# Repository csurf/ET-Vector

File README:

Eagle Tree Vector Flight Controller

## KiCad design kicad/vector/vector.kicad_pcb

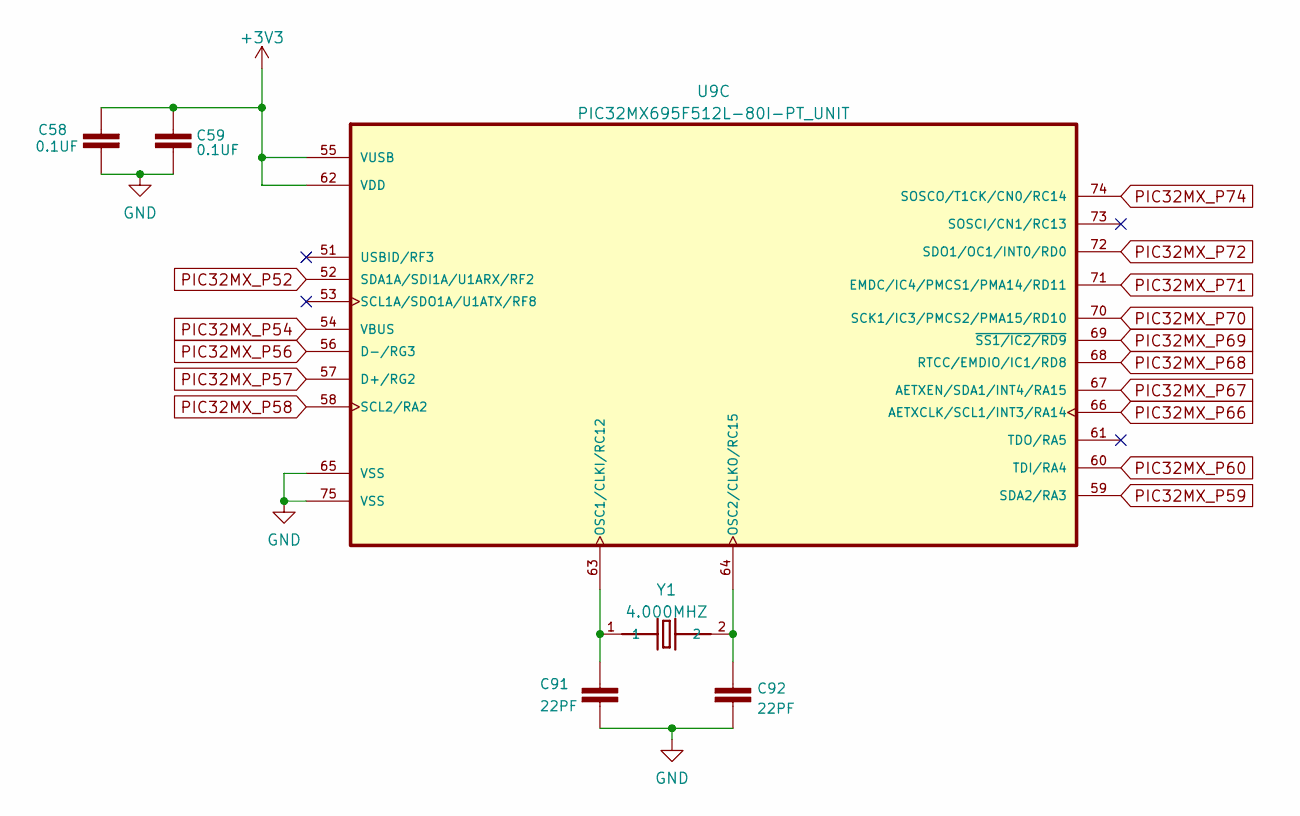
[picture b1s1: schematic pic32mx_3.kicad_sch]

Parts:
C58, C59: 0.1UF; C_0402_1005Metric
C91, C92: 22PF; C_0402_1005Metric
U9: PIC32MX695F512L-80I-PT_UNIT; TQFP-100_12x12mm_P0.4mm
Y1: 4.000MHZ; Crystal_SMD_HC49-SD

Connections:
+3V3: C58.2, C59.1, U9.55 (VUSB), U9.62 (VDD); also elsewhere on the board
GND: C58.1, C59.2, C91.2, C92.2, U9.65 (VSS), U9.75 (VSS); also elsewhere on the board
I2C_SCL2: U9.58 (SCL2/RA2); also elsewhere on the board
I2C_SDA2: U9.59 (SDA2/RA3); also elsewhere on the board
unnamed: C91.1, U9.63 (OSC1/CLKI/RC12), Y1.1
unnamed: C92.1, U9.64 (OSC2/CLKO/RC15), Y1.2
PIC32MX_P26: U9.68 (RTCC/EMDIO/IC1/RD8); also elsewhere on the board
PIC32MX_P40: U9.69 (~SS1/IC2/RD9); also elsewhere on the board
PIC32MX_P52: U9.52 (SDA1A/SDI1A/U1ARX/RF2), U9.71 (EMDC/IC4/PMCS1/PMA14/RD11); also elsewhere on the board
PIC32MX_P54: U9.54 (VBUS); also elsewhere on the board
PIC32MX_P56: U9.56 (D-/RG3); also elsewhere on the board
PIC32MX_P57: U9.57 (D+/RG2); also elsewhere on the board
PIC32MX_P60: U9.60 (TDI/RA4); also elsewhere on the board
PIC32MX_P66: U9.66 (AETXCLK/SCL1/INT3/RA14); also elsewhere on the board
PIC32MX_P67: U9.67 (AETXEN/SDA1/INT4/RA15); also elsewhere on the board
PIC32MX_P70: U9.70 (SCK1/IC3/PMCS2/PMA15/RD10); also elsewhere on the board
PIC32MX_P72: U9.72 (SDO1/OC1/INT0/RD0); also elsewhere on the board
PIC32MX_P74: U9.74 (SOSCO/T1CK/CN0/RC14); also elsewhere on the board

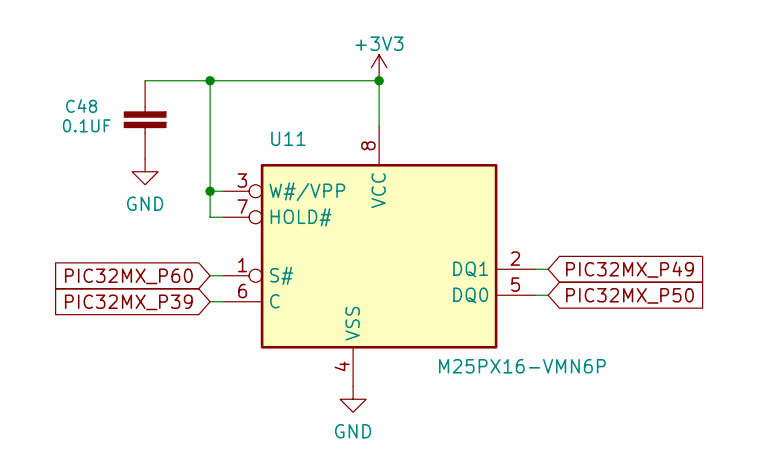
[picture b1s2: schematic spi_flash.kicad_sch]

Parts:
C48: 0.1UF; C_0402_1005Metric
U11: M25PX16-VMN6P; SOIC-8_3.9x4.9mm_P1.27mm

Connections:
+3V3: C48.2, U11.3 (W#/VPP), U11.7 (HOLD#), U11.8 (VCC); also elsewhere on the board
GND: C48.1, U11.4 (VSS); also elsewhere on the board
PIC32MX_P39: U11.6 (C); also elsewhere on the board
PIC32MX_P49: U11.2 (DQ1); also elsewhere on the board
PIC32MX_P50: U11.5 (DQ0); also elsewhere on the board
PIC32MX_P60: U11.1 (S#); also elsewhere on the board

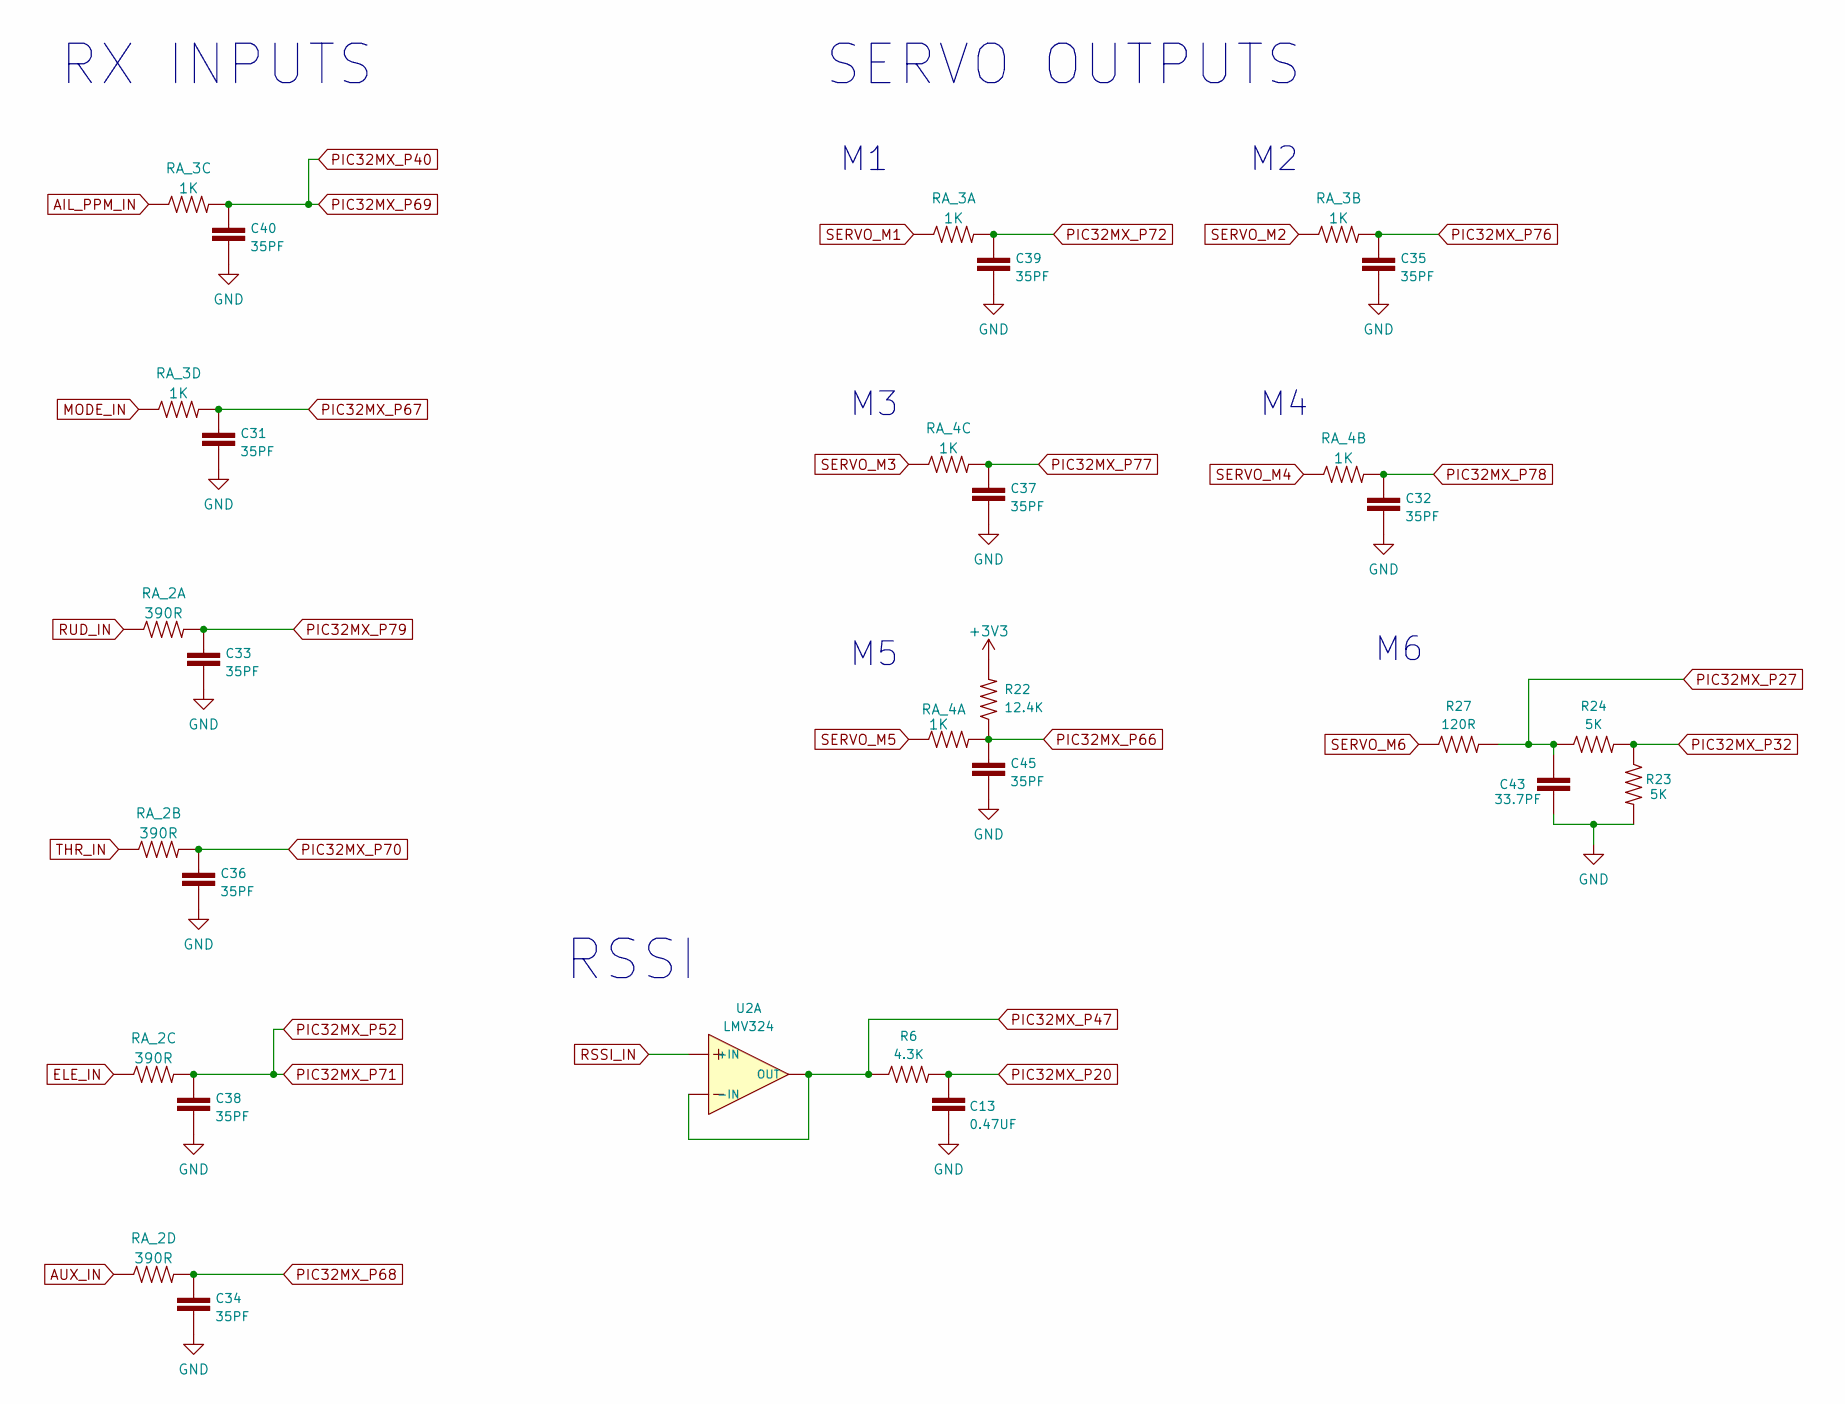
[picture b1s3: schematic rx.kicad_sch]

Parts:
C13: 0.47UF; C_0402_1005Metric
C31, C32, C33, C34, C35, C36, C37, C38, C39, C40, C45: 35PF; C_0402_1005Metric
C43: 33.7PF; C_0402_1005Metric
R6: 4.3K; R_0402_1005Metric
R22: 12.4K; R_0402_1005Metric
R23, R24: 5K; R_0402_1005Metric
R27: 120R; R_0402_1005Metric
RA_2: 390R; R_Array_Convex_4x0402
RA_3, RA_4: 1K; R_Array_Convex_4x0402
U2: LMV324; TSSOP-14_4.4x5mm_P0.65mm

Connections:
+3V3: R22.2; also elsewhere on the board
AIL_PPM_IN: RA_3.3 (1); also elsewhere on the board
AUX_IN: RA_2.4 (1); also elsewhere on the board
ELE_IN: RA_2.3 (1); also elsewhere on the board
GND: C13.2, C31.2, C32.2, C33.2, C34.2, C35.2, C36.2, C37.2, C38.2, C39.2, C40.2, C43.2, C45.2, R23.2; also elsewhere on the board
MODE_IN: RA_3.4 (1); also elsewhere on the board
PIC32MX_P20: C13.1, R6.2; also elsewhere on the board
PIC32MX_P26: C34.1, RA_2.5 (2); also elsewhere on the board
PIC32MX_P27: C43.1, R24.1, R27.2; also elsewhere on the board
PIC32MX_P32: R23.1, R24.2; also elsewhere on the board
PIC32MX_P40: C40.1, RA_3.6 (2); also elsewhere on the board
PIC32MX_P47: R6.1, U2.1 (OUT), U2.2 (-IN); also elsewhere on the board
PIC32MX_P52: C38.1, RA_2.6 (2); also elsewhere on the board
PIC32MX_P66: C45.1, R22.1, RA_4.8 (2); also elsewhere on the board
PIC32MX_P67: C31.1, RA_3.5 (2); also elsewhere on the board
PIC32MX_P70: C36.1, RA_2.7 (2); also elsewhere on the board
PIC32MX_P72: C39.1, RA_3.8 (2); also elsewhere on the board
PIC32MX_P76: C35.1, RA_3.7 (2); also elsewhere on the board
PIC32MX_P77: C37.1, RA_4.6 (2); also elsewhere on the board
PIC32MX_P78: C32.1, RA_4.7 (2); also elsewhere on the board
PIC32MX_P79: C33.1, RA_2.8 (2); also elsewhere on the board
RSSI_IN: U2.3 (+IN); also elsewhere on the board
RUD_IN: RA_2.1; also elsewhere on the board
SERVO_M1: RA_3.1; also elsewhere on the board
SERVO_M2: RA_3.2 (1); also elsewhere on the board
SERVO_M3: RA_4.3 (1); also elsewhere on the board
SERVO_M4: RA_4.2 (1); also elsewhere on the board
SERVO_M5: RA_4.1; also elsewhere on the board
SERVO_M6: R27.1; also elsewhere on the board
THR_IN: RA_2.2 (1); also elsewhere on the board

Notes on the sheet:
SERVO OUTPUTS
RSSI
RX INPUTS

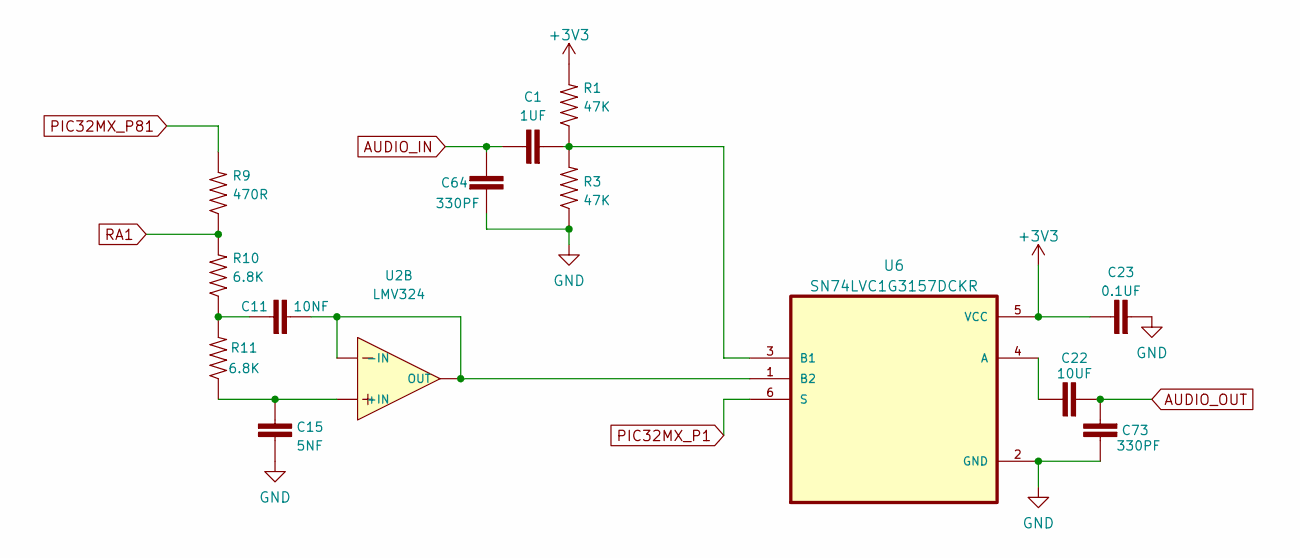
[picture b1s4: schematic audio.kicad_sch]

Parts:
C1: 1UF; C_0603_1608Metric
C11: 10NF; C_0402_1005Metric
C15: 5NF; C_0402_1005Metric
C22: 10UF; C_0603_1608Metric
C23: 0.1UF; C_0402_1005Metric
C64, C73: 330PF; C_0402_1005Metric
R1, R3: 47K; R_0402_1005Metric
R9: 470R; R_0402_1005Metric
R10, R11: 6.8K; R_0402_1005Metric
U2: LMV324; TSSOP-14_4.4x5mm_P0.65mm
U6: SN74LVC1G3157DCKR; Texas_R-PDSO-G6

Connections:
+3V3: C23.1, R1.2, U6.5 (VCC); also elsewhere on the board
AUDIO_IN: C1.1, C64.1; also elsewhere on the board
AUDIO_OUT: C22.2, C73.2; also elsewhere on the board
GND: C15.2, C23.2, C64.2, C73.1, R3.1, U6.2 (GND); also elsewhere on the board
unnamed: C1.2, R1.1, R3.2, U6.3 (B1)
unnamed: C11.1, R10.1, R11.2
unnamed: C11.2, U2.8 (OUT), U2.9 (-IN), U6.1 (B2)
unnamed: C15.1, R11.1, U2.10 (+IN)
unnamed: C22.1, U6.4 (A)
PIC32MX_P1: U6.6 (S); also elsewhere on the board
PIC32MX_P81: R9.2; also elsewhere on the board
RA1: R9.1, R10.2; also elsewhere on the board

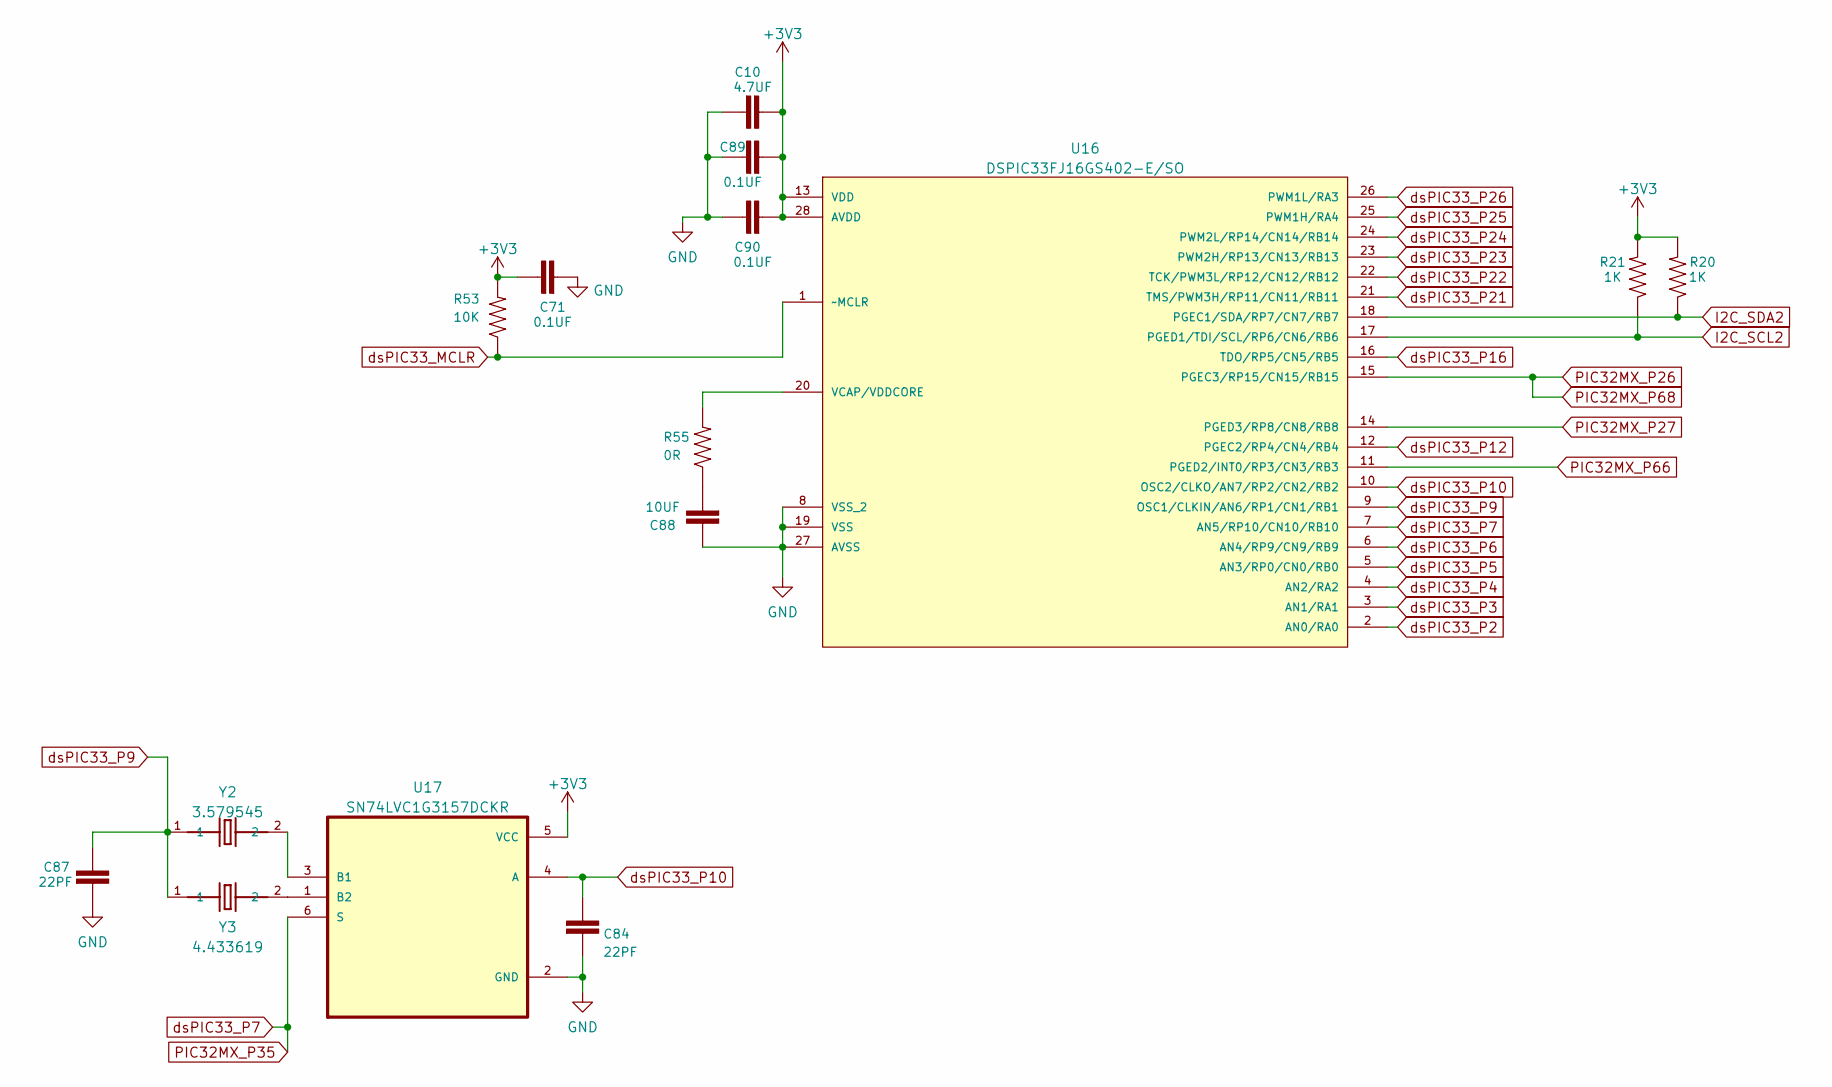
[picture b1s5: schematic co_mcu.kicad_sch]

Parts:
C10: 4.7UF; C_0603_1608Metric
C71, C89, C90: 0.1UF; C_0402_1005Metric
C84, C87: 22PF; C_0402_1005Metric
C88: 10UF; C_0805_2012Metric
R20, R21: 1K; R_0402_1005Metric
R53: 10K; R_0402_1005Metric
R55: 0R; R_0402_1005Metric
U16: DSPIC33FJ16GS402-E/SO; SOIC-28W_7.5x17.9mm_P1.27mm; MPN DSPIC33FJ16GS402-E/SO
U17: SN74LVC1G3157DCKR; Texas_R-PDSO-G6
Y2: 3.579545; Crystal_SMD_HC49-SD
Y3: 4.433619; Crystal_SMD_HC49-SD

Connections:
+3V3: C10.1, C71.1, C89.2, C90.2, R20.2, R21.2, R53.2, U16.13 (VDD), U16.28 (AVDD), U17.5 (VCC); also elsewhere on the board
GND: C10.2, C71.2, C84.2, C87.2, C88.1, C89.1, C90.1, U16.8 (VSS_2), U16.19 (VSS), U16.27 (AVSS), U17.2 (GND); also elsewhere on the board
I2C_SCL2: R21.1, U16.17 (PGED1/TDI/SCL/RP6/CN6/RB6); also elsewhere on the board
I2C_SDA2: R20.1, U16.18 (PGEC1/SDA/RP7/CN7/RB7); also elsewhere on the board
unnamed: C88.2, R55.1
unnamed: R55.2, U16.20 (VCAP/VDDCORE)
unnamed: U17.1 (B2), Y3.2
unnamed: U17.3 (B1), Y2.2
PIC32MX_P26: U16.15 (PGEC3/RP15/CN15/RB15); also elsewhere on the board
PIC32MX_P27: U16.14 (PGED3/RP8/CN8/RB8); also elsewhere on the board
PIC32MX_P35: U16.7 (AN5/RP10/CN10/RB10), U17.6 (S); also elsewhere on the board
PIC32MX_P66: U16.11 (PGED2/INT0/RP3/CN3/RB3); also elsewhere on the board
dsPIC33_MCLR: R53.1, U16.1 (~MCLR)
dsPIC33_P2: U16.2 (AN0/RA0); also elsewhere on the board
dsPIC33_P3: U16.3 (AN1/RA1); also elsewhere on the board
dsPIC33_P4: U16.4 (AN2/RA2); also elsewhere on the board
dsPIC33_P5: U16.5 (AN3/RP0/CN0/RB0); also elsewhere on the board
dsPIC33_P6: U16.6 (AN4/RP9/CN9/RB9); also elsewhere on the board
dsPIC33_P9: C87.1, U16.9 (OSC1/CLKIN/AN6/RP1/CN1/RB1), Y2.1, Y3.1
dsPIC33_P10: C84.1, U16.10 (OSC2/CLKO/AN7/RP2/CN2/RB2), U17.4 (A)
dsPIC33_P12: U16.12 (PGEC2/RP4/CN4/RB4); also elsewhere on the board
dsPIC33_P16: U16.16 (TDO/RP5/CN5/RB5); also elsewhere on the board
dsPIC33_P21: U16.21 (TMS/PWM3H/RP11/CN11/RB11); also elsewhere on the board
dsPIC33_P22: U16.22 (TCK/PWM3L/RP12/CN12/RB12); also elsewhere on the board
dsPIC33_P23: U16.23 (PWM2H/RP13/CN13/RB13); also elsewhere on the board
dsPIC33_P24: U16.24 (PWM2L/RP14/CN14/RB14); also elsewhere on the board
dsPIC33_P25: U16.25 (PWM1H/RA4); also elsewhere on the board
dsPIC33_P26: U16.26 (PWM1L/RA3); also elsewhere on the board

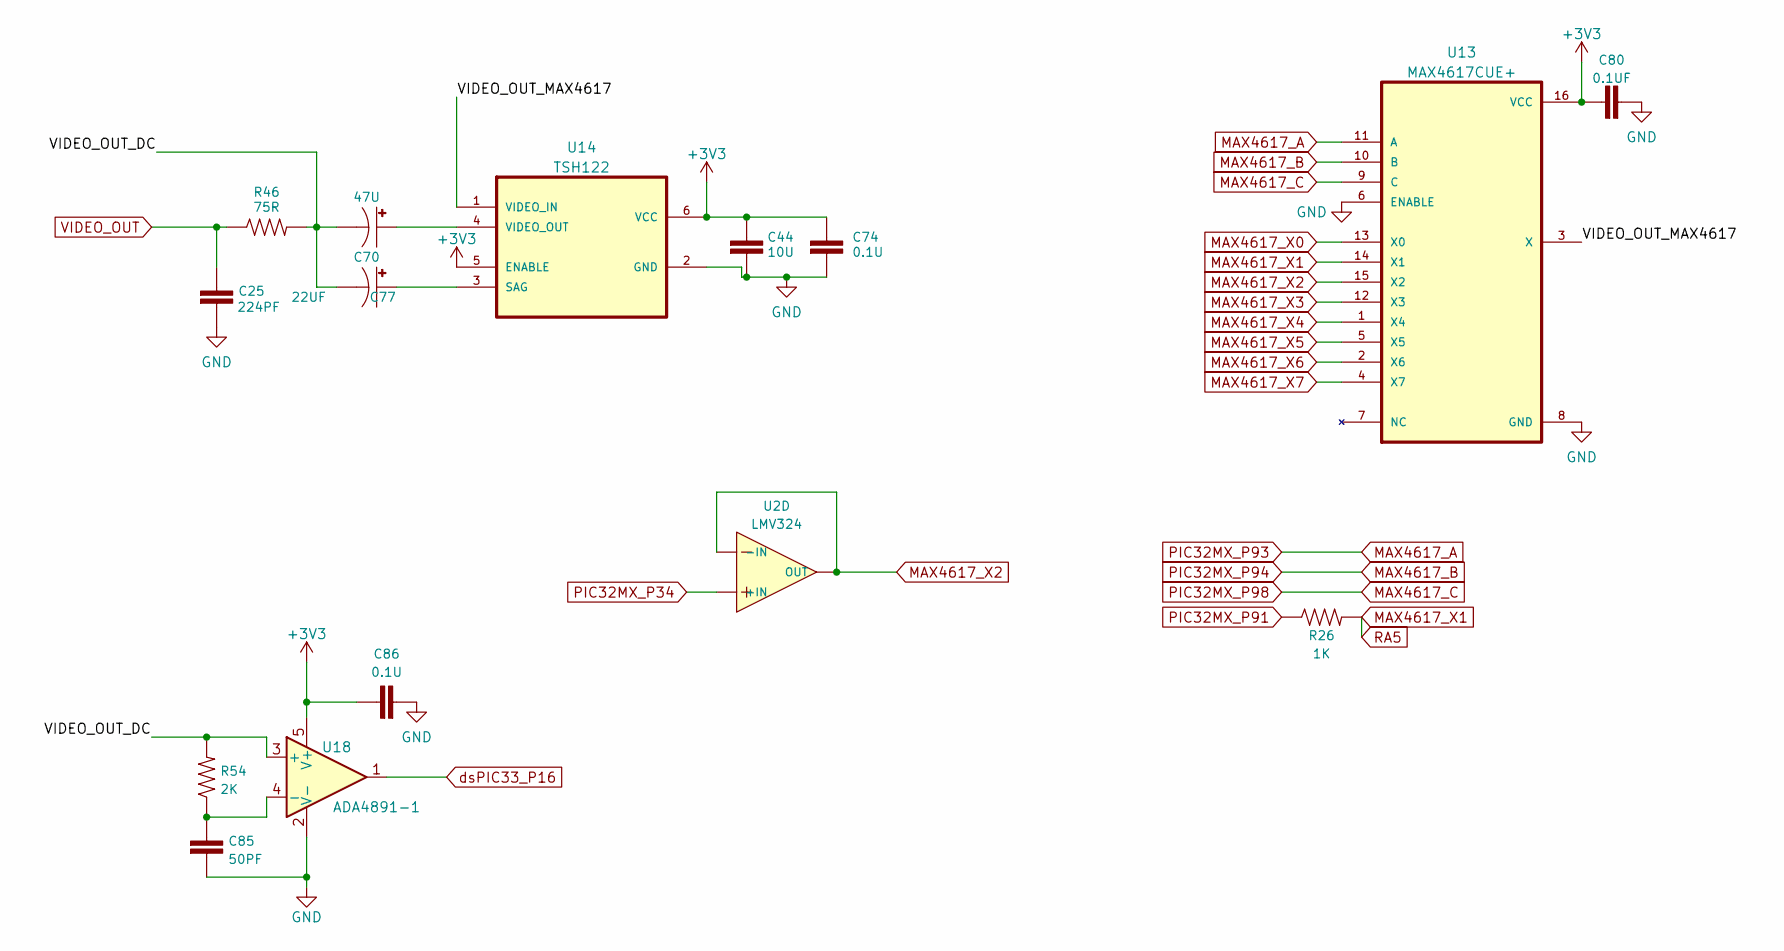
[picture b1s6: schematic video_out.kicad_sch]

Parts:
C25: 224PF; C_0402_1005Metric
C44: 10U; C_0805_2012Metric
C70: 47U; CP_EIA-3528-12_Kemet-T
C74, C86: 0.1U; C_0402_1005Metric
C77: 22UF; CP_EIA-3528-12_Kemet-T
C80: 0.1UF; C_0402_1005Metric
C85: 50PF; C_0402_1005Metric
R26: 1K; R_0402_1005Metric
R46: 75R; R_0402_1005Metric
R54: 2K; R_0402_1005Metric
U2: LMV324; TSSOP-14_4.4x5mm_P0.65mm
U13: MAX4617CUE+; TSSOP-16_4.4x5mm_P0.65mm
U14: TSH122; SOT-363_SC-70-6
U18: ADA4891-1; SOT-23-5

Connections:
+3V3: C44.1, C74.1, C80.1, C86.1, U13.16 (VCC), U14.5 (ENABLE), U14.6 (VCC), U18.5 (V+); also elsewhere on the board
/VIDEO_OUT/VIDEO_OUT_DC: C70.2 (-), C77.2 (-), R46.2, R54.2, U18.3 (+)
/VIDEO_OUT/VIDEO_OUT_MAX4617: U13.3 (X), U14.1 (VIDEO_IN)
GND: C25.2, C44.2, C74.2, C80.2, C85.2, C86.2, U13.6 (ENABLE), U13.8 (GND), U14.2 (GND), U18.2 (V-); also elsewhere on the board
MAX4617_A: U13.11 (A); also elsewhere on the board
MAX4617_B: U13.10 (B); also elsewhere on the board
MAX4617_C: U13.9 (C); also elsewhere on the board
MAX4617_X0: U13.13 (X0); also elsewhere on the board
MAX4617_X1: R26.2, U13.14 (X1); also elsewhere on the board
MAX4617_X2: U2.13 (-IN), U2.14 (OUT), U13.15 (X2)
MAX4617_X3: U13.12 (X3); also elsewhere on the board
MAX4617_X4: U13.1 (X4); also elsewhere on the board
MAX4617_X5: U13.5 (X5); also elsewhere on the board
MAX4617_X6: U13.2 (X6); also elsewhere on the board
MAX4617_X7: U13.4 (X7); also elsewhere on the board
unnamed: C70.1 (+), U14.4 (VIDEO_OUT)
unnamed: C77.1 (+), U14.3 (SAG)
unnamed: C85.1, R54.1, U18.4 (-)
PIC32MX_P34: U2.12 (+IN); also elsewhere on the board
PIC32MX_P91: R26.1; also elsewhere on the board
VIDEO_OUT: C25.1, R46.1; also elsewhere on the board
dsPIC33_P16: U18.1; also elsewhere on the board

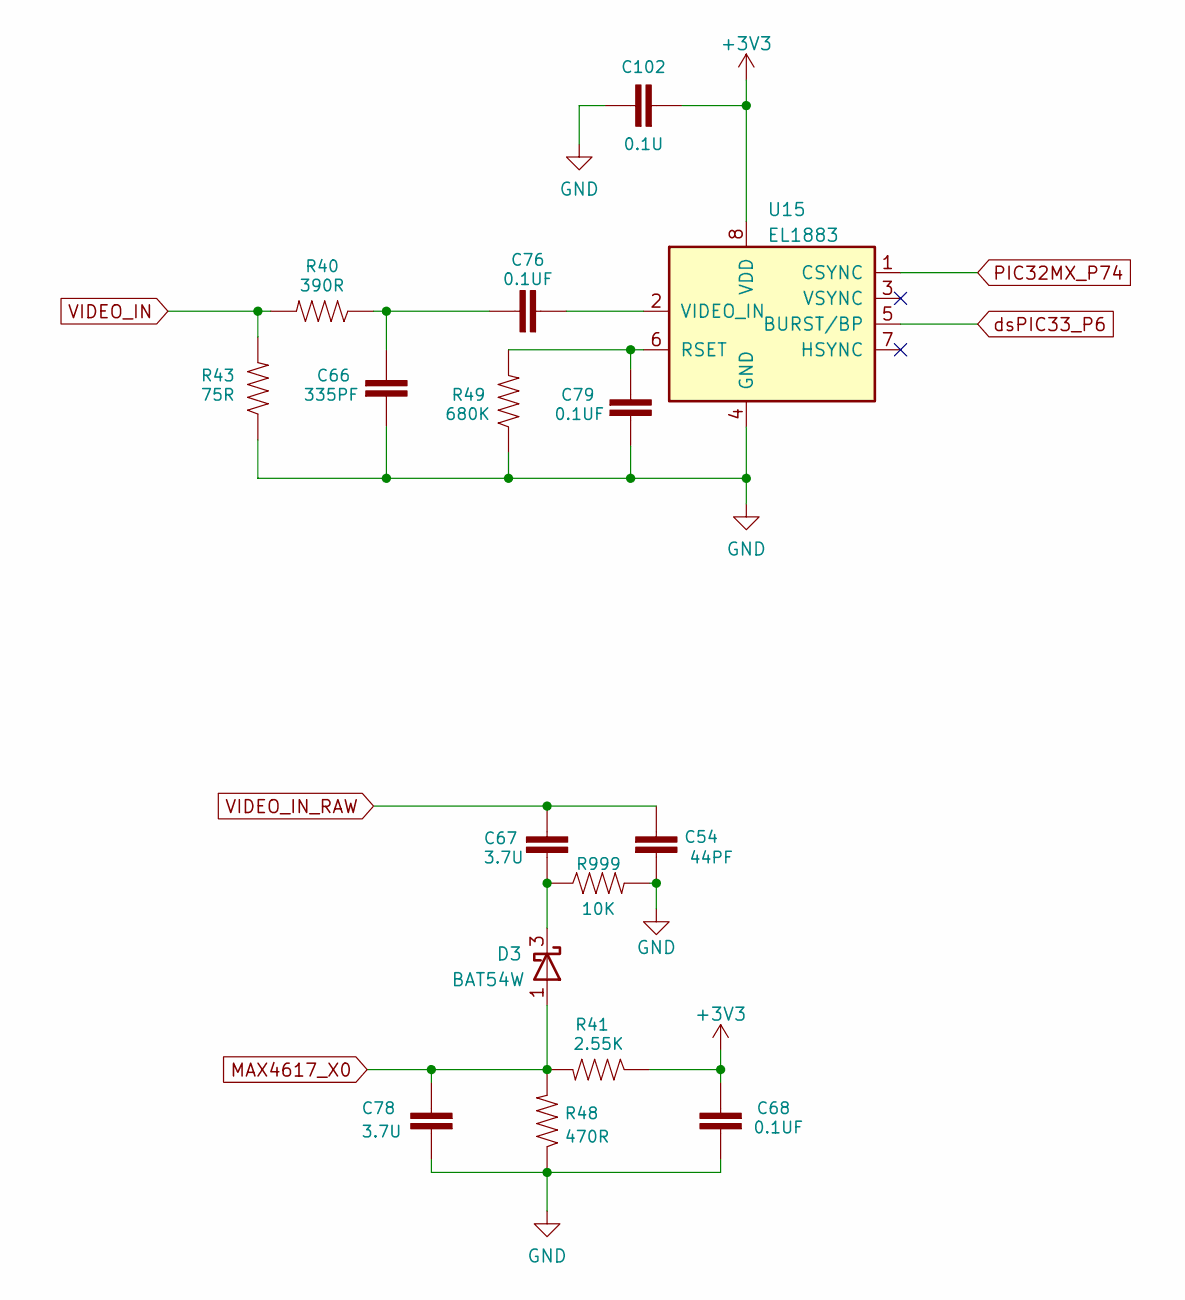
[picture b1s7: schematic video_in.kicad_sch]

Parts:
C54: 44PF; C_0402_1005Metric
C66: 335PF; C_0402_1005Metric
C67, C78: 3.7U; C_0603_1608Metric
C68, C76, C79: 0.1UF; C_0402_1005Metric
C102: 0.1U; C_0402_1005Metric
D3: BAT54W; SOT-323_SC-70
R40: 390R; R_0402_1005Metric
R41: 2.55K; R_0402_1005Metric
R43: 75R; R_0402_1005Metric
R48: 470R; R_0402_1005Metric
R49: 680K; R_0402_1005Metric
R999: 10K; R_0402_1005Metric
U15: EL1883; SOIC-8_3.9x4.9mm_P1.27mm

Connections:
+3V3: C68.1, C102.2, R41.1, U15.8 (VDD); also elsewhere on the board
GND: C54.2, C66.2, C68.2, C78.2, C79.2, C102.1, R43.1, R48.1, R49.1, R999.2, U15.4 (GND); also elsewhere on the board
MAX4617_X0: C78.1, D3.1 (A), R41.2, R48.2; also elsewhere on the board
unnamed: C66.1, C76.1, R40.1
unnamed: C67.2, D3.3 (K), R999.1
unnamed: C76.2, U15.2 (VIDEO_IN)
unnamed: C79.1, R49.2, U15.6 (RSET)
PIC32MX_P74: U15.1 (CSYNC); also elsewhere on the board
VIDEO_IN: R40.2, R43.2; also elsewhere on the board
VIDEO_IN_RAW: C54.1, C67.1
dsPIC33_P6: U15.5 (BURST/BP); also elsewhere on the board

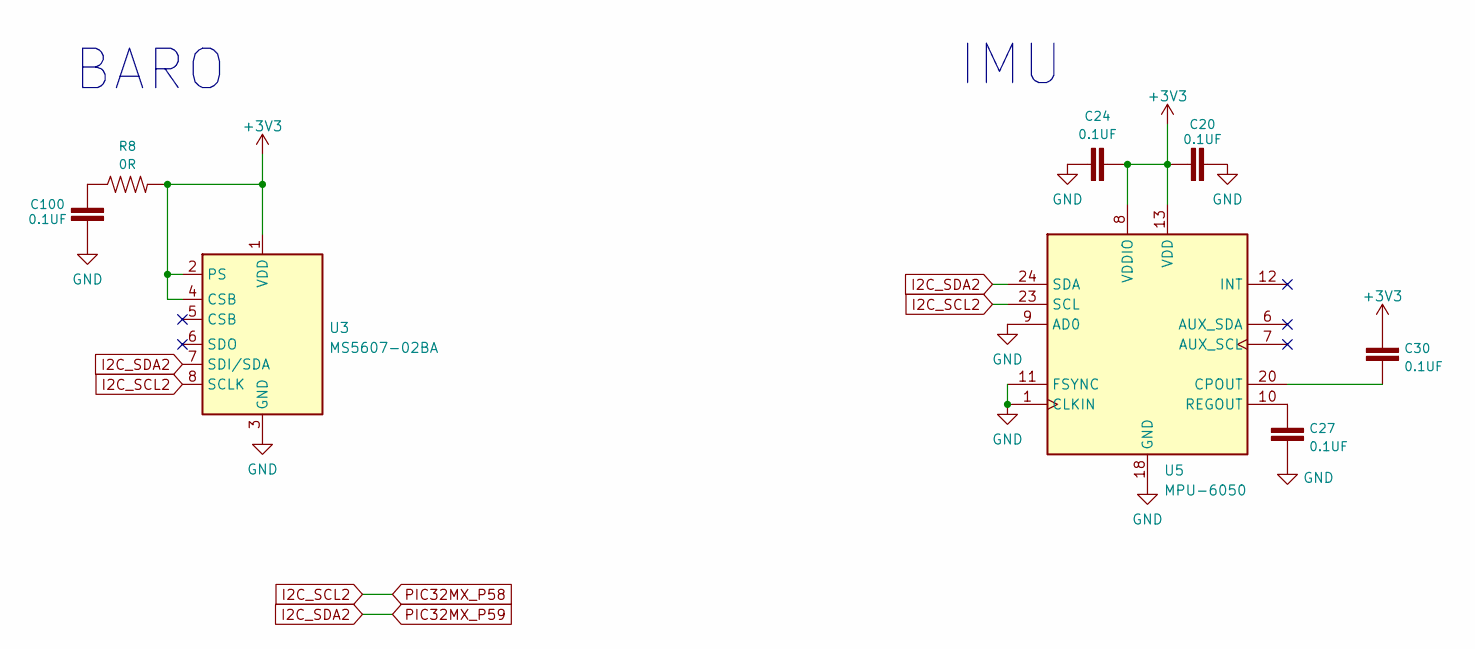
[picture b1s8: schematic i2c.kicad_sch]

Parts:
C20, C24, C27, C30, C100: 0.1UF; C_0402_1005Metric
R8: 0R; R_0402_1005Metric
U3: MS5607-02BA; LGA-8_3x5mm_P1.25mm
U5: MPU-6050; InvenSense_QFN-24_4x4mm_P0.5mm

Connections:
+3V3: C20.1, C24.2, C30.2, R8.2, U3.1 (VDD), U3.2 (PS), U3.4 (CSB), U5.8 (VDDIO), U5.13 (VDD); also elsewhere on the board
GND: C20.2, C24.1, C27.2, C100.2, U3.3 (GND), U5.1 (CLKIN), U5.9 (AD0), U5.11 (FSYNC), U5.18 (GND); also elsewhere on the board
I2C_SCL2: U3.8 (SCLK), U5.23 (SCL); also elsewhere on the board
I2C_SDA2: U3.7 (SDI/SDA), U5.24 (SDA); also elsewhere on the board
unnamed: C27.1, U5.10 (REGOUT)
unnamed: C30.1, U5.20 (CPOUT)
unnamed: C100.1, R8.1

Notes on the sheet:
BARO
IMU

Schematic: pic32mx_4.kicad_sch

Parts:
C52: 10UF; C_0805_2012Metric
C57: 0.1UF; C_0402_1005Metric
DS1: GRN; LED_1206_3216Metric
DS2: RED; LED_1206_3216Metric
R30: 75R; R_0402_1005Metric
RA_5: 390; R_Array_Convex_4x0402
U9: PIC32MX695F512L-80I-PT_UNIT; TQFP-100_12x12mm_P0.4mm

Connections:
+3V3: C57.1, U9.86 (VDD); also elsewhere on the board
GND: C52.2, C57.2, R30.2, RA_5.5 (2); also elsewhere on the board
MAX4617_A: U9.93 (PMD0/RE0); also elsewhere on the board
MAX4617_B: U9.94 (PMD1/RE1); also elsewhere on the board
MAX4617_C: U9.98 (PMD2/RE2); also elsewhere on the board
MAX4617_X1: RA_5.1, RA_5.2 (1), RA_5.3 (1), RA_5.4 (1); also elsewhere on the board
unnamed: C52.1, U9.85 (VCAP/VDDCORE)
unnamed: DS1.1 (A), U9.96 (TRD1/RG12)
unnamed: DS1.2 (C), DS2.2 (C), R30.1
unnamed: DS2.1 (A), U9.97 (TRD0/RG13)
unnamed: RA_5.6 (2), U9.87 (ETXD1/PMD11/RF0)
unnamed: RA_5.7 (2), U9.88 (ETXD0/PMD10/RF1)
unnamed: RA_5.8 (2), U9.90 (PMD8/RG0)
PIC32MX_P76: U9.76 (OC2/RD1); also elsewhere on the board
PIC32MX_P77: U9.77 (OC3/RD2); also elsewhere on the board
PIC32MX_P78: U9.78 (OC4/RD3); also elsewhere on the board
PIC32MX_P79: U9.79 (ETXD2/IC5/PMD12/RD12); also elsewhere on the board
PIC32MX_P81: U9.81 (OC5/PMWR/CN13/RD4); also elsewhere on the board
PIC32MX_P91: U9.91 (TRCLK/RA6); also elsewhere on the board

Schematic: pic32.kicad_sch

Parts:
C56, C61: 0.1UF; C_0402_1005Metric
P7: C_0603_1608Metric
R29: 10K; R_0402_1005Metric
RA_1: 1K; R_Array_Convex_4x0402
U9: PIC32MX695F512L-80I-PT_UNIT; TQFP-100_12x12mm_P0.4mm

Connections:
+3V3: C56.2, C61.2, R29.2, U9.2 (VDD), U9.16 (VDD); also elsewhere on the board
GND: C56.1, C61.1, RA_1.4 (1), U9.15 (VSS); also elsewhere on the board
unnamed: P7.1 (A), U9.24 (PGEC1/AN1/CN3/RB1)
unnamed: P7.2 (B), U9.25 (PGED1/AN0/CN2/RB0)
unnamed: RA_1.6 (2), U9.6 (T2CK/RC1)
unnamed: RA_1.7 (2), U9.7 (T3CK/RC2)
unnamed: RA_1.8 (2), U9.8 (T4CK/RC3)
PIC32MX_MCLR: R29.1, U9.13 (~MCLR)
PIC32MX_P1: U9.1 (AERXERR/RG15); also elsewhere on the board
PIC32MX_P10: U9.10 (ECOL/SCK2A/U2BTX/~U2ARTS/PMA5/CN8/RG6); also elsewhere on the board
PIC32MX_P11: U9.11 (ECRS/SDA2A/SDI2A/U2ARX/PMA4/CN9/RG7); also elsewhere on the board
PIC32MX_P12: U9.12 (ERXDV/SCL2A/SDO2A/U2ATX/PMA3/CN10/RG8); also elsewhere on the board
PIC32MX_P14: U9.14 (ERXCLK/~SS2A/U2BRX/U2ACTS/PMA2/CN11/RG9); also elsewhere on the board
PIC32MX_P20: U9.20 (AN5/C1IN+/VBUSON/CN7/RB5); also elsewhere on the board
PIC32MX_P21: U9.21 (AN4/C1IN-/CN6/RB4); also elsewhere on the board
RA1: RA_1.1, RA_1.2 (1), RA_1.3 (1), RA_1.5 (2); also elsewhere on the board

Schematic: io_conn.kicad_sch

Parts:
C4: 36PF; C_0402_1005Metric
C5: 35PF; C_0402_1005Metric
C12, C14: 224PF; C_0402_1005Metric
C53: 0.1UF; C_0402_1005Metric
JP1: USB_B_Mini; USB_Mini-B_Lumberg_2486_01_Horizontal
P1, P2, P9: JST_ZH_4P; JST_ZH_S4B-ZH-A_1x04_P1.50mm_Horizontal
P3: JST_PHD_7P; JST_PHD_S14B-PHDSS_2x07_P2.00mm_Horizontal
P4: MCLR; PinHeader_1x02_P1.00mm_Vertical
P5: Conn_03x07_servo; PinHeader_3x07_P2.54mm_Horizontal
P6: JST_PHD_4P; JST_PHD_S8B-PHDSS_2x04_P2.00mm_Horizontal
R2, R7: 1K; R_0402_1005Metric
R4, R5: 1.5K; R_0402_1005Metric
R25: 4K; R_0402_1005Metric
RA_4: 1K; R_Array_Convex_4x0402
RL1, RL2: 150R; R_0402_1005Metric

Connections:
5V_BACKUP: P5.20 (Pin_7); also elsewhere on the board
5V_PM: P3.9; also elsewhere on the board
12V_PM: P3.8
+3V3: R4.2, R5.2; also elsewhere on the board
+5V: C53.1, P1.1, P9.1; also elsewhere on the board
/IO CONNECTOR/5V_motor: P5.2 (Pin_1), P5.5 (Pin_2), P5.8 (Pin_3), P5.11 (Pin_4), P5.14 (Pin_5), P5.17 (Pin_6), P6.2, R25.2
AIL_PPM_IN: P6.3; also elsewhere on the board
AUDIO_IN: P2.2; also elsewhere on the board
AUDIO_OUT: P2.1; also elsewhere on the board
AUX_IN: P6.8; also elsewhere on the board
ELE_IN: P6.7; also elsewhere on the board
GND: C4.2, C5.2, C12.2, C14.2, C53.2, JP1.5 (GND), JP1.6 (Shield), P1.2, P2.4, P3.3, P3.4, P3.10, P3.11, P3.13, P5.3 (Pin_1), P5.6 (Pin_2), P5.9 (Pin_3), P5.12 (Pin_4), P5.15 (Pin_5), P5.18 (Pin_6), P5.21 (Pin_7), P6.1, P9.2, RA_4.4 (1); also elsewhere on the board
MODE_IN: P6.4; also elsewhere on the board
unnamed: C5.1, P1.3, R2.2
unnamed: P1.4, R7.2
unnamed: P9.3, R4.1, RL1.2
unnamed: P9.4, R5.1, RL2.2
PIC32MX_P10: R2.1; also elsewhere on the board
PIC32MX_P11: C12.1, RL2.1; also elsewhere on the board
PIC32MX_P12: C14.1, RL1.1; also elsewhere on the board
PIC32MX_P13: P4.2
PIC32MX_P14: C4.1, R7.1; also elsewhere on the board
PIC32MX_P21: R25.1, RA_4.5 (2); also elsewhere on the board
PIC32MX_P54: JP1.1 (VBUS); also elsewhere on the board
PIC32MX_P56: JP1.2 (D-); also elsewhere on the board
PIC32MX_P57: JP1.3 (D+); also elsewhere on the board
RSSI_IN: P5.19 (Pin_7); also elsewhere on the board
RUD_IN: P6.5; also elsewhere on the board
SERVO_M1: P5.1; also elsewhere on the board
SERVO_M2: P5.4 (Pin_2); also elsewhere on the board
SERVO_M3: P5.7 (Pin_3); also elsewhere on the board
SERVO_M4: P5.10 (Pin_4); also elsewhere on the board
SERVO_M5: P5.13 (Pin_5); also elsewhere on the board
SERVO_M6: P5.16 (Pin_6); also elsewhere on the board
THR_IN: P6.6; also elsewhere on the board
VCAM_MIC: P2.3, P3.5, P3.14; also elsewhere on the board
VIDEO_IN: P3.6; also elsewhere on the board
VIDEO_OUT: P3.1; also elsewhere on the board
V_SENSE: P3.7; also elsewhere on the board
V_VTX: P3.2, P3.12; also elsewhere on the board
dsPIC33_P1: P4.1

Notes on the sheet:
SCL4
SERVO
USB
5V OUTPUT RAIL SENSE
MCLR
RX_IN
AUDIO
UART
SDA4
I2C_4 BUS
VIDEO
U6RX
U6TX

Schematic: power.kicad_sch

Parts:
C2, C18, C55: 10NF; C_0402_1005Metric
C3, C28, C29, C46, C81, C82: 0.1UF; C_0402_1005Metric
C41, C42: 10UF; C_0603_1608Metric
D1, D2, D6: 1N5817; D_SOD-323
R12: 0R; R_0402_1005Metric
R13, R15, R16, R19: 1K; R_0402_1005Metric
R14, R17, R18: 17K; R_0402_1005Metric
U2: LMV324; TSSOP-14_4.4x5mm_P0.65mm
U66: RT9193-33GB; SOT-23-5

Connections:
5V_BACKUP: C46.2, D6.2 (A); also elsewhere on the board
5V_PM: C2.1, D1.2 (A); also elsewhere on the board
+3V3: C3.1, R12.1, U2.4 (V+), U66.5 (VOUT); also elsewhere on the board
+5V: C41.1, C82.1, D1.1 (K), D2.1 (K), D6.1 (K), U66.1 (VIN), U66.3 (EN); also elsewhere on the board
GND: C2.2, C3.2, C18.2, C28.2, C29.2, C41.2, C42.2, C46.1, C55.2, C81.1, C82.2, R15.1, R16.1, R19.1, U2.11 (V-), U66.2 (GND); also elsewhere on the board
unnamed: C42.1, R12.2
unnamed: C81.2, U66.4 (BP)
PIC32MX_P22: R16.2, R17.1
PIC32MX_P23: R14.1, R15.2
PIC32MX_P33: R13.1; also elsewhere on the board
PIC32MX_P44: C28.1, R18.1, R19.2; also elsewhere on the board
PIC32MX_P54: D2.2 (A); also elsewhere on the board
PM_12V: R18.2
VCAM_MIC: C55.1, R17.2; also elsewhere on the board
V_SENSE: C29.1, R13.2; also elsewhere on the board
V_VTX: C18.1, R14.2; also elsewhere on the board

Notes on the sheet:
3.3V POWER
VOLTAGE SENSE

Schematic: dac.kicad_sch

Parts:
C49, C50, C51, C69, C72, C75: 0.1UF; C_0402_1005Metric
C93: 50PF; C_0402_1005Metric
C94, C95, C96, C97: 220PF; C_0402_1005Metric
R32, R47: 3K; R_0402_1005Metric
R33: 1.8K; R_0402_1005Metric
R34, R45: 2.5K; R_0402_1005Metric
R36: 2.2K; R_0402_1005Metric
R37: 4.3K; R_0402_1005Metric
R38: 3.48K; R_0402_1005Metric
R44: 10K; R_0402_1005Metric
R50: 3.58K; R_0402_1005Metric
R51: 5K; R_0402_1005Metric
R52: 2.4K; R_0402_1005Metric
R56: 1.5K; R_0402_1005Metric
RA_8: 2.4K; R_Array_Convex_4x0402
RA_9: 1.5K; R_Array_Convex_4x0402
U2: LMV324; TSSOP-14_4.4x5mm_P0.65mm

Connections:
GND: C75.2, R52.2, R56.2, RA_8.1, RA_8.4 (1), RA_8.6 (2), RA_8.7 (2), RA_9.5 (2), RA_9.6 (2), RA_9.7 (2), RA_9.8 (2); also elsewhere on the board
MAX4617_X3: C50.2, R37.1, RA_8.3 (1); also elsewhere on the board
MAX4617_X4: C51.2, R38.1, RA_8.5 (2); also elsewhere on the board
MAX4617_X5: C49.2, R36.1, RA_8.8 (2); also elsewhere on the board
MAX4617_X6: C72.2, R51.1, RA_8.2 (1); also elsewhere on the board
MAX4617_X7: C69.2, R50.1, R52.1; also elsewhere on the board
unnamed: C49.1, C95.1, R32.2, R56.1
unnamed: C50.1, C93.1, R33.2, RA_9.1
unnamed: C51.1, C94.1, R34.2, RA_9.3 (1)
unnamed: C69.1, C97.1, R45.2, RA_9.4 (1)
unnamed: C72.1, C96.1, R47.2, RA_9.2 (1)
unnamed: C75.1, R44.2, U2.5 (+IN)
unnamed: R36.2, R37.2, R38.2, R50.2, R51.2, U2.6 (-IN), U2.7 (OUT)
dsPIC33_P2: C95.2; also elsewhere on the board
dsPIC33_P3: C97.2; also elsewhere on the board
dsPIC33_P4: C94.2; also elsewhere on the board
dsPIC33_P5: C96.2; also elsewhere on the board
dsPIC33_P12: C93.2; also elsewhere on the board
dsPIC33_P21: R32.1; also elsewhere on the board
dsPIC33_P22: R47.1; also elsewhere on the board
dsPIC33_P23: R33.1; also elsewhere on the board
dsPIC33_P24: R44.1; also elsewhere on the board
dsPIC33_P25: R34.1; also elsewhere on the board
dsPIC33_P26: R45.1; also elsewhere on the board

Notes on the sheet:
*** UNCERTAIN

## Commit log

2024-03-22 add pics & update kicad files
